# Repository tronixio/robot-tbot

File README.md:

# ROBOT - TBOT 2 Wheels.

## TBOT Features.

- 2 Wheels.
- Continuous RC Servos Motors.
- Power 2xCells 18650 Lithium Ion Rechargeable Batteries, with embedded charger.
- [PARALLAX Small Robot Chassis.](https://www.parallax.com/product/700-00022)
- [PARALLAX Feedback 360 High Speed Servo.](https://www.parallax.com/product/900-00360)
- [PARALLAX Small Robot Whell and Tire.](https://www.parallax.com/product/28114)
- [PARALLAX 1" Tail Whell Ball.](https://www.parallax.com/product/700-00009)

## TBOT All Schematics.

- [DRAFT - MCU Board PIC-8BIT.](https://github.com/tronixio/robot-tbot/)
- [Charger 2x18650.](https://github.com/tronixio/robot-tbot/blob/main/Kicad/charger/extras/schematic.pdf)
- [DRAFT - IR Wheel.](https://github.com/tronixio/robot-tbot/)
- [Sensor GP2Y.](https://github.com/tronixio/robot-tbot/blob/main/Kicad/gp2y/extras/schematic.pdf)
- [DRAFT - Sensor HC-SR04.](https://github.com/tronixio/robot-tbot/)
- [DRAFT - IR Line Folllow.](https://github.com/tronixio/robot-tbot/)

## TBOT Code.

- [PIC16F1778 - MCU & GPIO Configuration.](https://github.com/tronixio/robot-tbot/blob/main/Code/configuration/)
- [PIC16F1778 - EUSART TX - Display Strings.](https://github.com/tronixio/robot-tbot/blob/main/Code/eusart-tx/)
- [PIC16F1778 - EUSART TX/RX - Echo RX Character.](https://github.com/tronixio/robot-tbot/blob/main/Code/eusart-txrx/)
- [PIC16F1778 - ADC/TIMER0 - Read, Display & Check Battery Value.](https://github.com/tronixio/robot-tbot/blob/main/Code/adc/)
- [PIC16F1778 - PWM 16-Bit - RC Servo Forward & Backward.](https://github.com/tronixio/robot-tbot/blob/main/Code/pwm/)
- [PIC16F1778 - INT0 - Emergency Switch & LED.](https://github.com/tronixio/robot-tbot/blob/main/Code/int0/)
- [PIC16F1778 - IOC - Sharp GP2Y0D21YK.](https://github.com/tronixio/robot-tbot/blob/main/Code/gp2y0d21yk/)

## TBOT Firmware.

- [DRAFT - PIC16F1778 - PIC-AS - Firmware SHARP GP2Y0D21YK.](https://github.com/tronixio/robot-tbot/blob/main/MplabX/PICAS-P16F1778-GP2Y0D21YK.X/)

<!--
* [PIC16F1778 - XC8 - Firmware DEBUG.](https://github.com/tronixio/robot-tbot/tree/main/MplabX/XC8-P16F1778-DEBUG.X/)
* [TBOT Firmware - Sharp GP2Y0D21YK.](https://github.com/tronixio/robot-tbot/tree/main/MplabX/PICAS-P16F1778-GP2Y0D21YK.X)
* [TBOT Firmware - Sharp GP2Y0A21YK.](https://github.com/tronixio/robot-tbot/tree/main/MplabX/PICAS-P16F1778-GP2Y0A21YK.X)
* [TBOT Firmware - HC SR04.](https://github.com/tronixio/robot-tbot/tree/main/MplabX/PICAS-P16F1778-HCSR04.X)
-->

## DRAFT - TBOT MCU PIC 8Bit Top.

## DRAFT - TBOT MCU PIC 8Bit Bottom.

## TBOT Charger Top.

## TBOT Charger Bottom.

## DRAFT - TBOT IR Wheel Top.

## DRAFT - TBOT IR Wheel Bottom.

## TBOT GP2Y Top.

## TBOT GP2Y Bottom.

## DRAFT - TBOT HC-SR04 Top.

## DRAFT - TBOT HC-SR04 Bottom.

## DRAFT - TBOT IR Line Follow Top.

## DRAFT - TBOT IR Line Follow Bottom.

!!! note

    - DRAFT : Prototype OK, last check schematic, PCB & code can be modify.
    - TODO : Work in progress, prototype was not good, hardware, PCB and code can be rework.

!!! example "DISCLAIMER"

    THIS CODE IS PROVIDED WITHOUT ANY WARRANTY OR GUARANTEES.
    USERS MAY USE THIS CODE FOR DEVELOPMENT AND EXAMPLE PURPOSES ONLY.
    AUTHORS ARE NOT RESPONSIBLE FOR ANY ERRORS, OMISSIONS, OR DAMAGES THAT COULD
    RESULT FROM USING THIS FIRMWARE IN WHOLE OR IN PART.

---

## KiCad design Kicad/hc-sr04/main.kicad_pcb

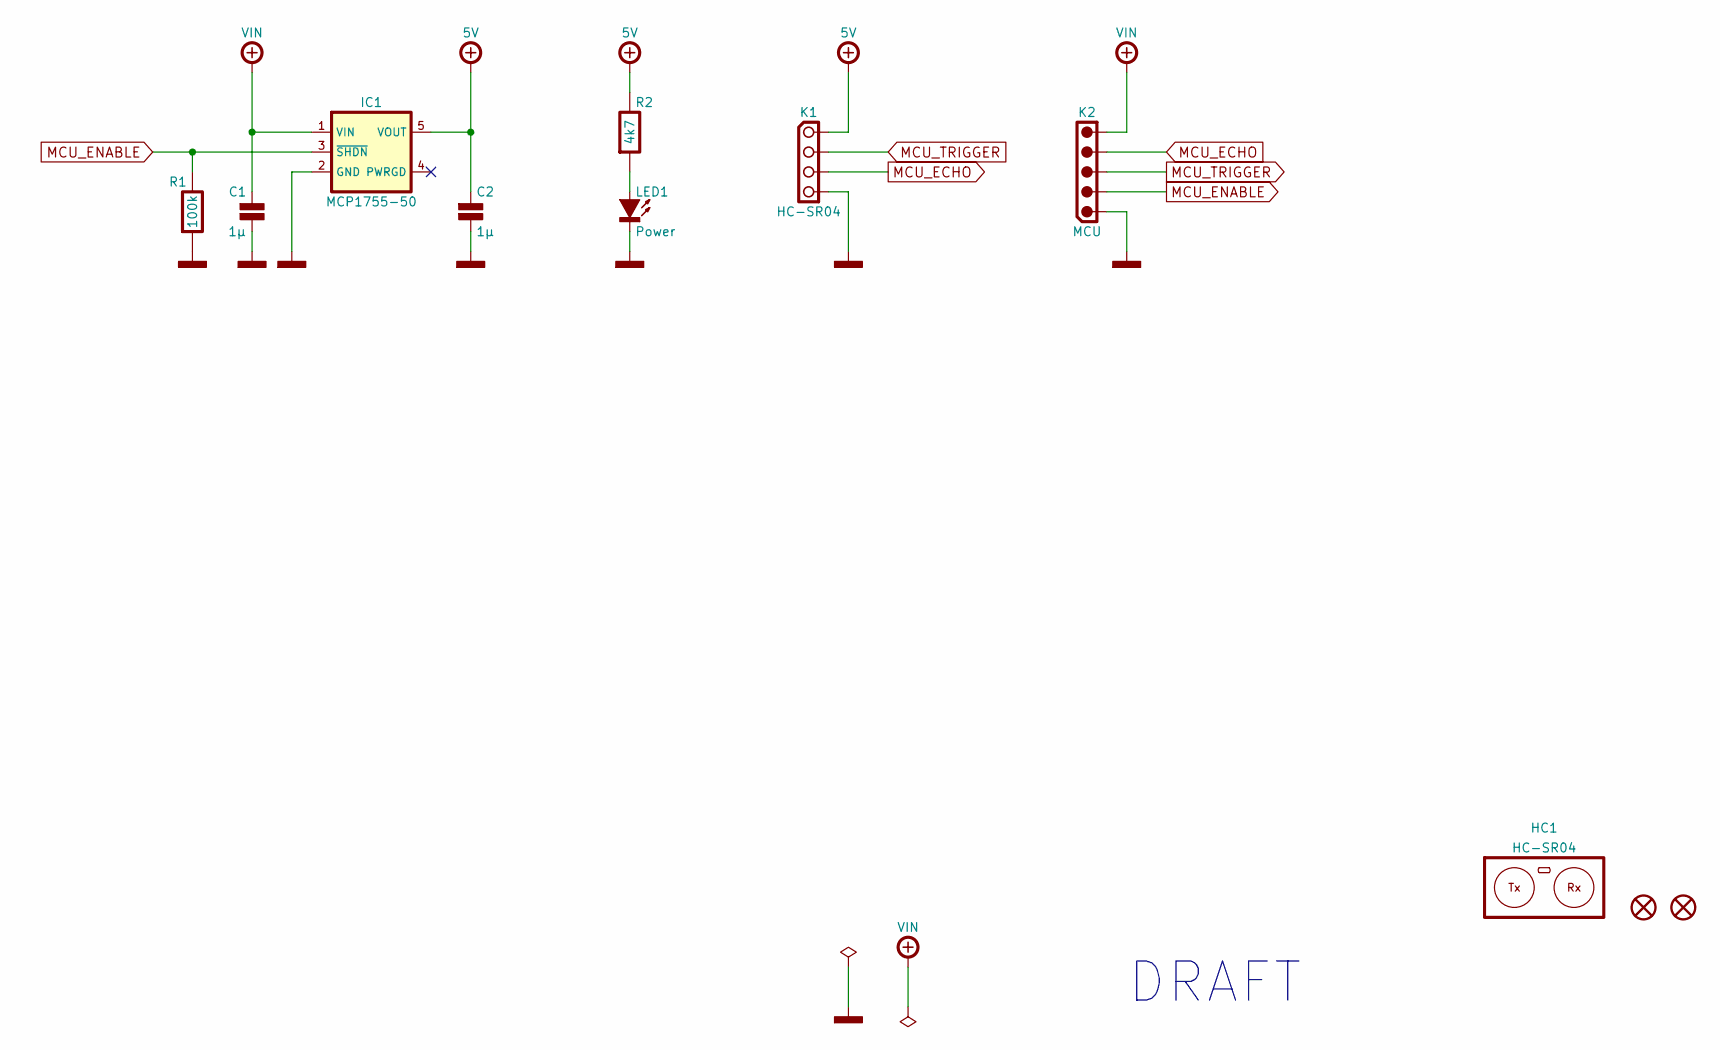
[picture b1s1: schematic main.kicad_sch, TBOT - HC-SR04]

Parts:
C1, C2: 1µ; CAPACITOR-SMD-1206; Voltage 16V; Tolerance 10%; Mouser 80-C1206C105K4R
H1, H2: MOUNTING-HOLE-3MM-MASK
HC1: HC-SR04
IC1: MCP1755-50; SOT-23-5; Mouser 579-MCP1755T-5002EOT
K1: HC-SR04; SAMTEC-SSW-104-02-T-S-RA; Mouser 200-SSW10402TSRA
K2: MCU; MOLEX-532540570; Mouser 538-53254-0570
LED1: Power; LED-SMD-1206; Mouser 604-APTR3216-VFX
R1: 100k; RESISTOR-SMD-1206; Tolerance 5%; Mouser 660-RK73B2BTTDD104J
R2: 4k7; RESISTOR-SMD-1206; Tolerance 5%; Mouser 660-RK73B2BTTDD472J

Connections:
+5V: C2.1, IC1.5 (VOUT), K1.1, R2.1
+VIN: C1.1, IC1.1 (VIN), K2.5
GND: C1.2, C2.2, IC1.2 (GND), K1.4, K2.1, LED1.1 (C), R1.2
MCU_ECHO: K1.3, K2.4
MCU_ENABLE: IC1.3 (~SHDN), K2.2, R1.1
MCU_TRIGGER: K1.2, K2.3
unnamed: LED1.2 (A), R2.2

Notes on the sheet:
DRAFT

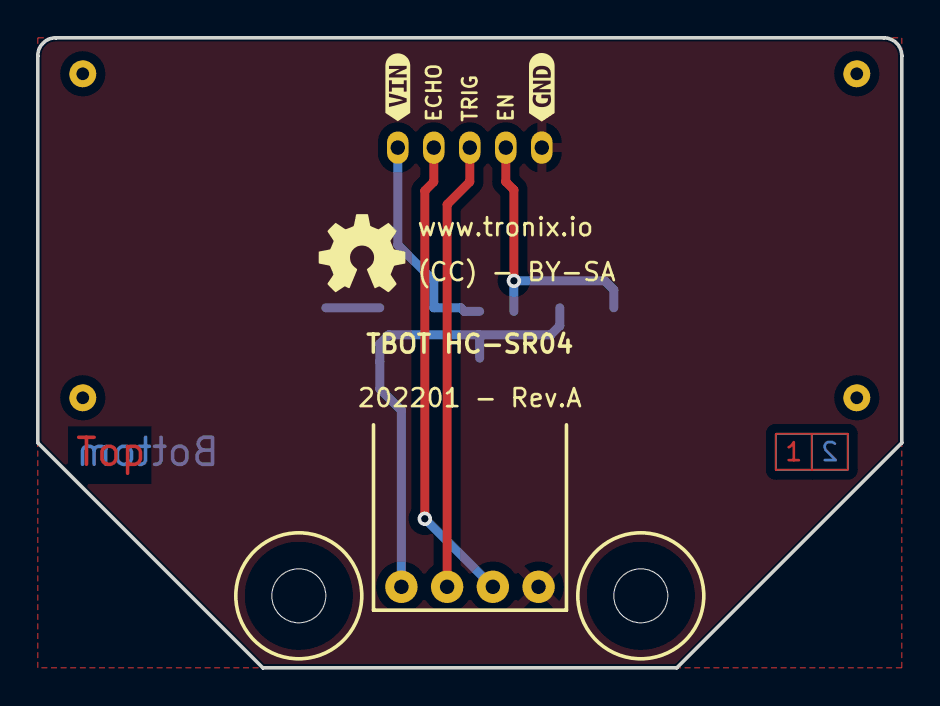
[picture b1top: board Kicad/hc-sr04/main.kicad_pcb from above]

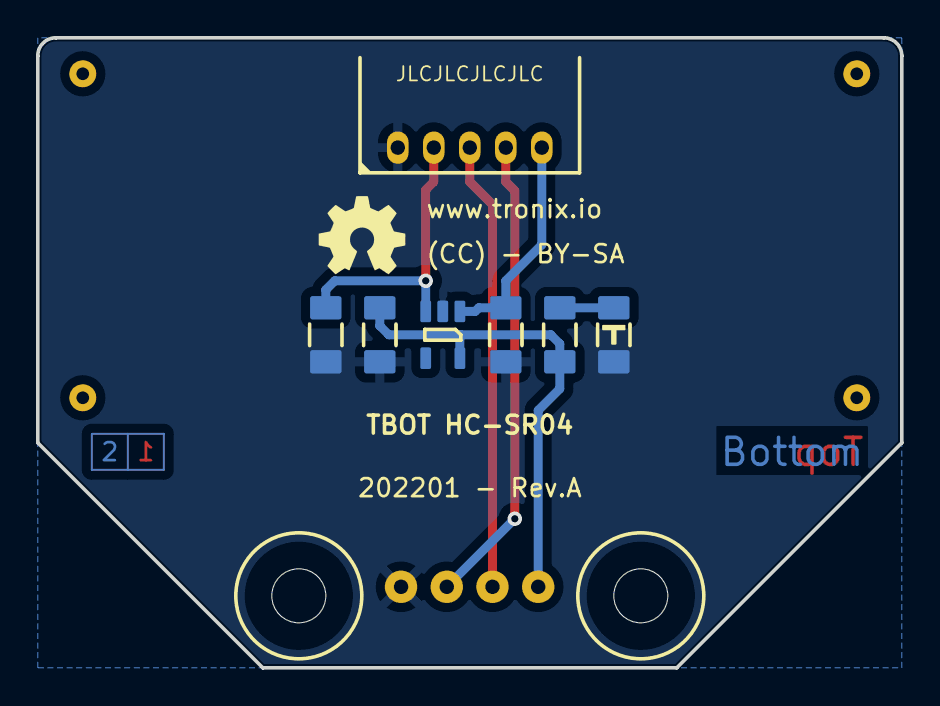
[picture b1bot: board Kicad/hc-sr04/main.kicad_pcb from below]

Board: 2 copper layers, 48.0 x 35.0 mm, 15 parts (10 on the bottom side), 7 nets.

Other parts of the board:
GB: LOGO; OSHW-5MM
GT: LOGO; OSHW-5MM
kibuzzard-6288C61E: G***; kibuzzard-6288C61E
kibuzzard-6288C626: G***; kibuzzard-6288C626

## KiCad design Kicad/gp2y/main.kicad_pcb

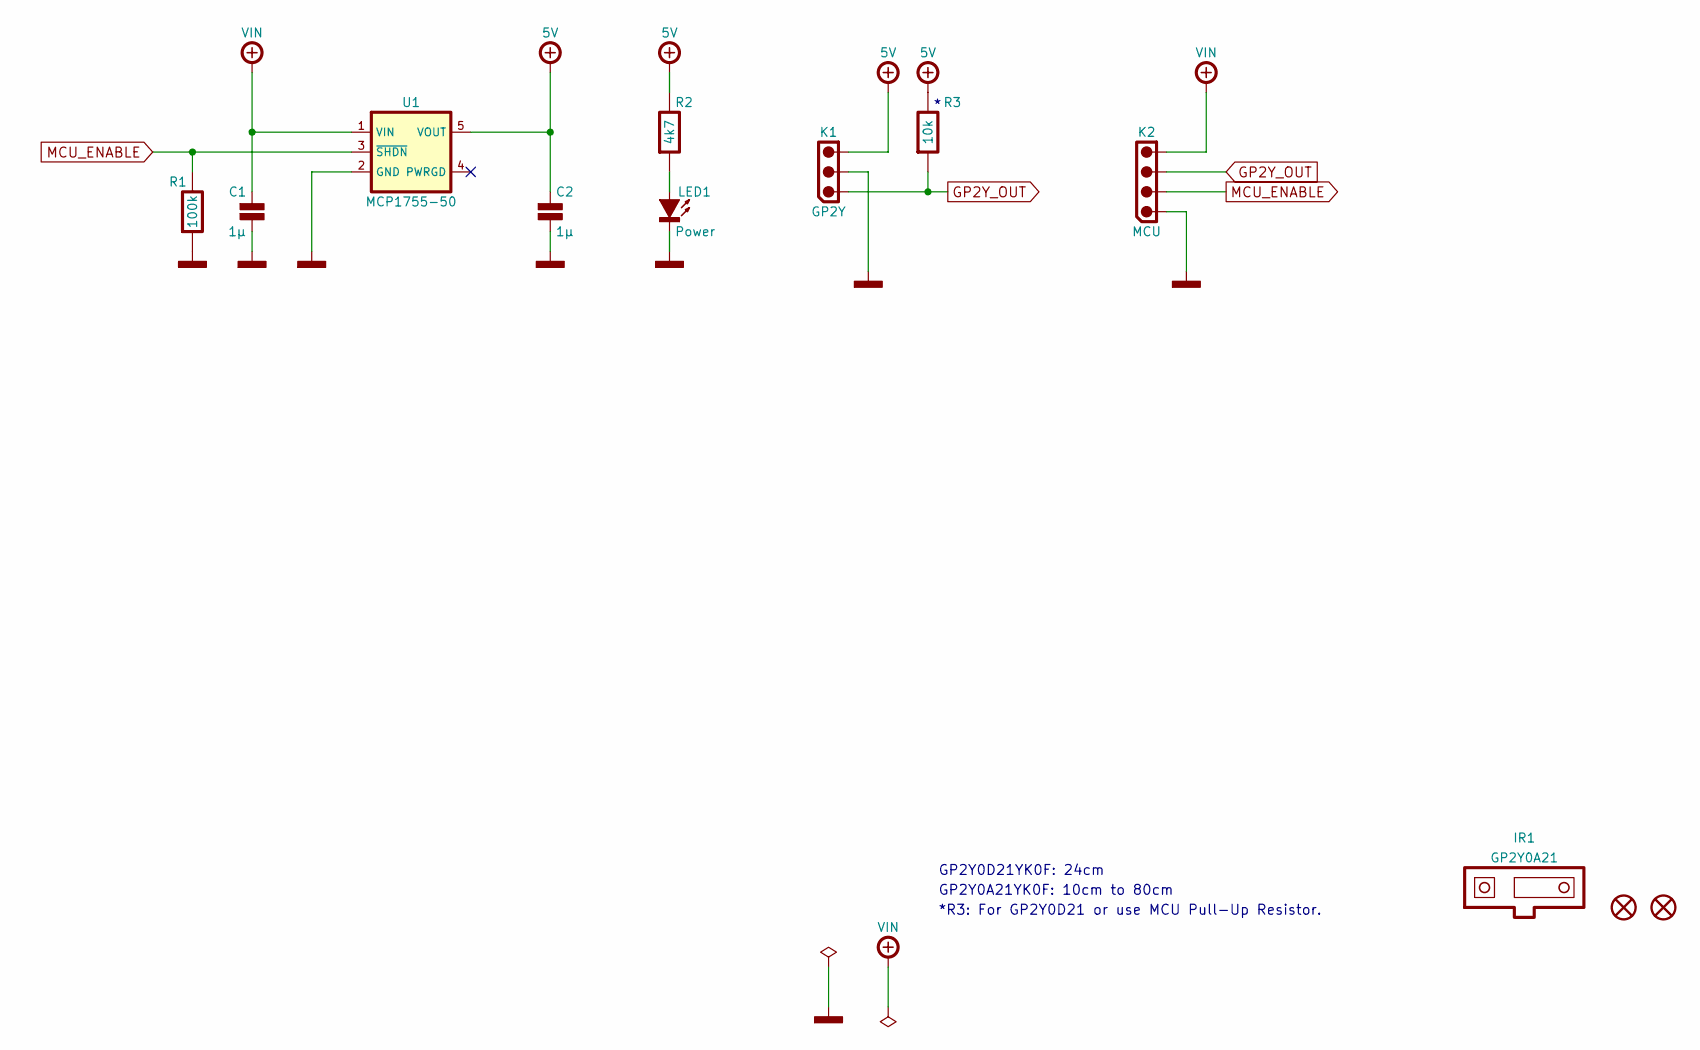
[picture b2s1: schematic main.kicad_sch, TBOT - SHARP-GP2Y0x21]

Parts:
C1, C2: 1µ; CAPACITOR-SMD-1206; Voltage 16V; Tolerance 10%; Mouser 80-C1206C105K4R
H1, H2: MOUNTING-HOLE-3MM-MASK
IR1: GP2Y0A21; SHARP-GP2Y0A; Mouser 852-GP2Y0A21YK0F
K1: GP2Y; MOLEX-532540370; Mouser 538-53254-0370
K2: MCU; MOLEX-532540470; Mouser 538-53254-0470
LED1: Power; LED-SMD-1206; Mouser 604-APTR3216-VFX
R1: 100k; RESISTOR-SMD-1206; Tolerance 5%; Mouser 660-RK73B2BTTDD104J
R2: 4k7; RESISTOR-SMD-1206; Tolerance 5%; Mouser 660-RK73B2BTTDD472J
R3: 10k; RESISTOR-SMD-1206; Tolerance 5%; Mouser 660-RK73B2BTTDD103J
U1: MCP1755-50; SOT-23-5; Mouser 579-MCP1755T-5002EOT

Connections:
+5V: C2.1, K1.3, R2.1, R3.1, U1.5 (VOUT)
+VIN: C1.1, K2.4, U1.1 (VIN)
GND: C1.2, C2.2, K1.2, K2.1, LED1.1 (C), R1.2, U1.2 (GND)
GP2Y_OUT: K1.1, K2.3, R3.2
MCU_ENABLE: K2.2, R1.1, U1.3 (~SHDN)
unnamed: LED1.2 (A), R2.2

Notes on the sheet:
GP2Y0D21YK0F: 24cm
GP2Y0A21YK0F: 10cm to 80cm
*R3: For GP2Y0D21 or use MCU Pull-Up Resistor.

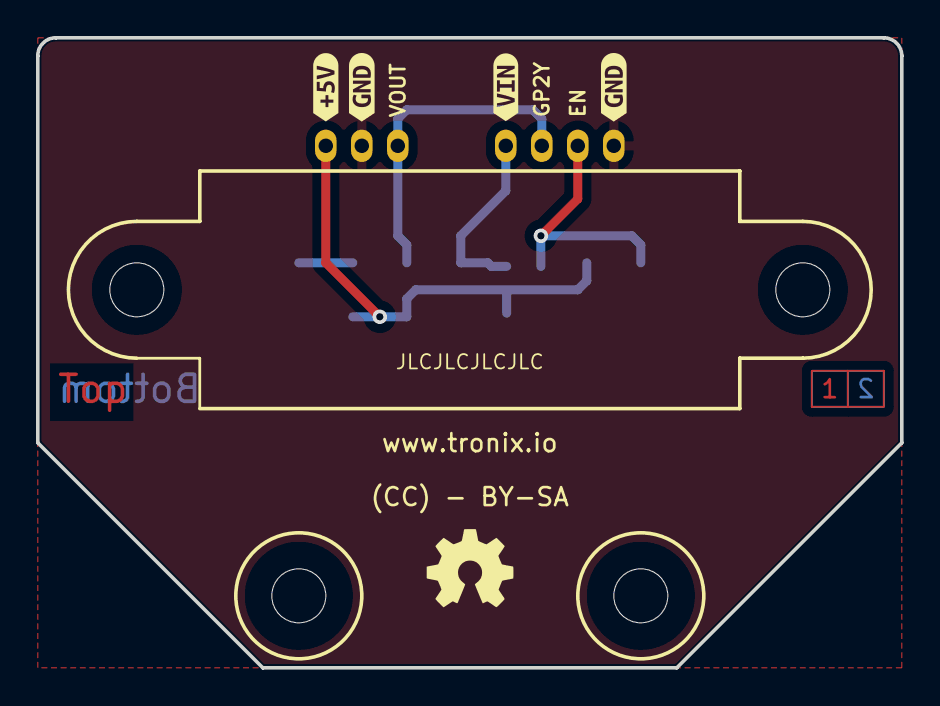
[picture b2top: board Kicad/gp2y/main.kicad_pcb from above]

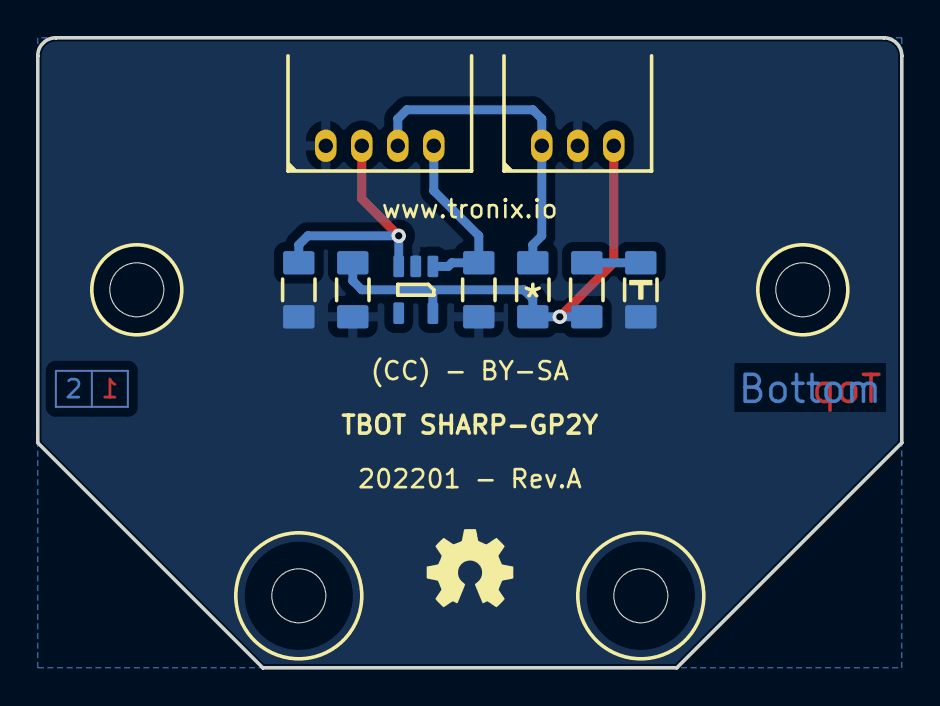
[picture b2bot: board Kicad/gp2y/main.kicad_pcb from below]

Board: 2 copper layers, 48.0 x 35.0 mm, 18 parts (12 on the bottom side), 6 nets.

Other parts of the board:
GB: LOGO; OSHW-5MM
GT: LOGO; OSHW-5MM
kibuzzard-6288C56E: G***; kibuzzard-6288C56E
kibuzzard-6288C554: G***; kibuzzard-6288C554
kibuzzard-6288C562: G***; kibuzzard-6288C562
kibuzzard-6288C567: G***; kibuzzard-6288C567

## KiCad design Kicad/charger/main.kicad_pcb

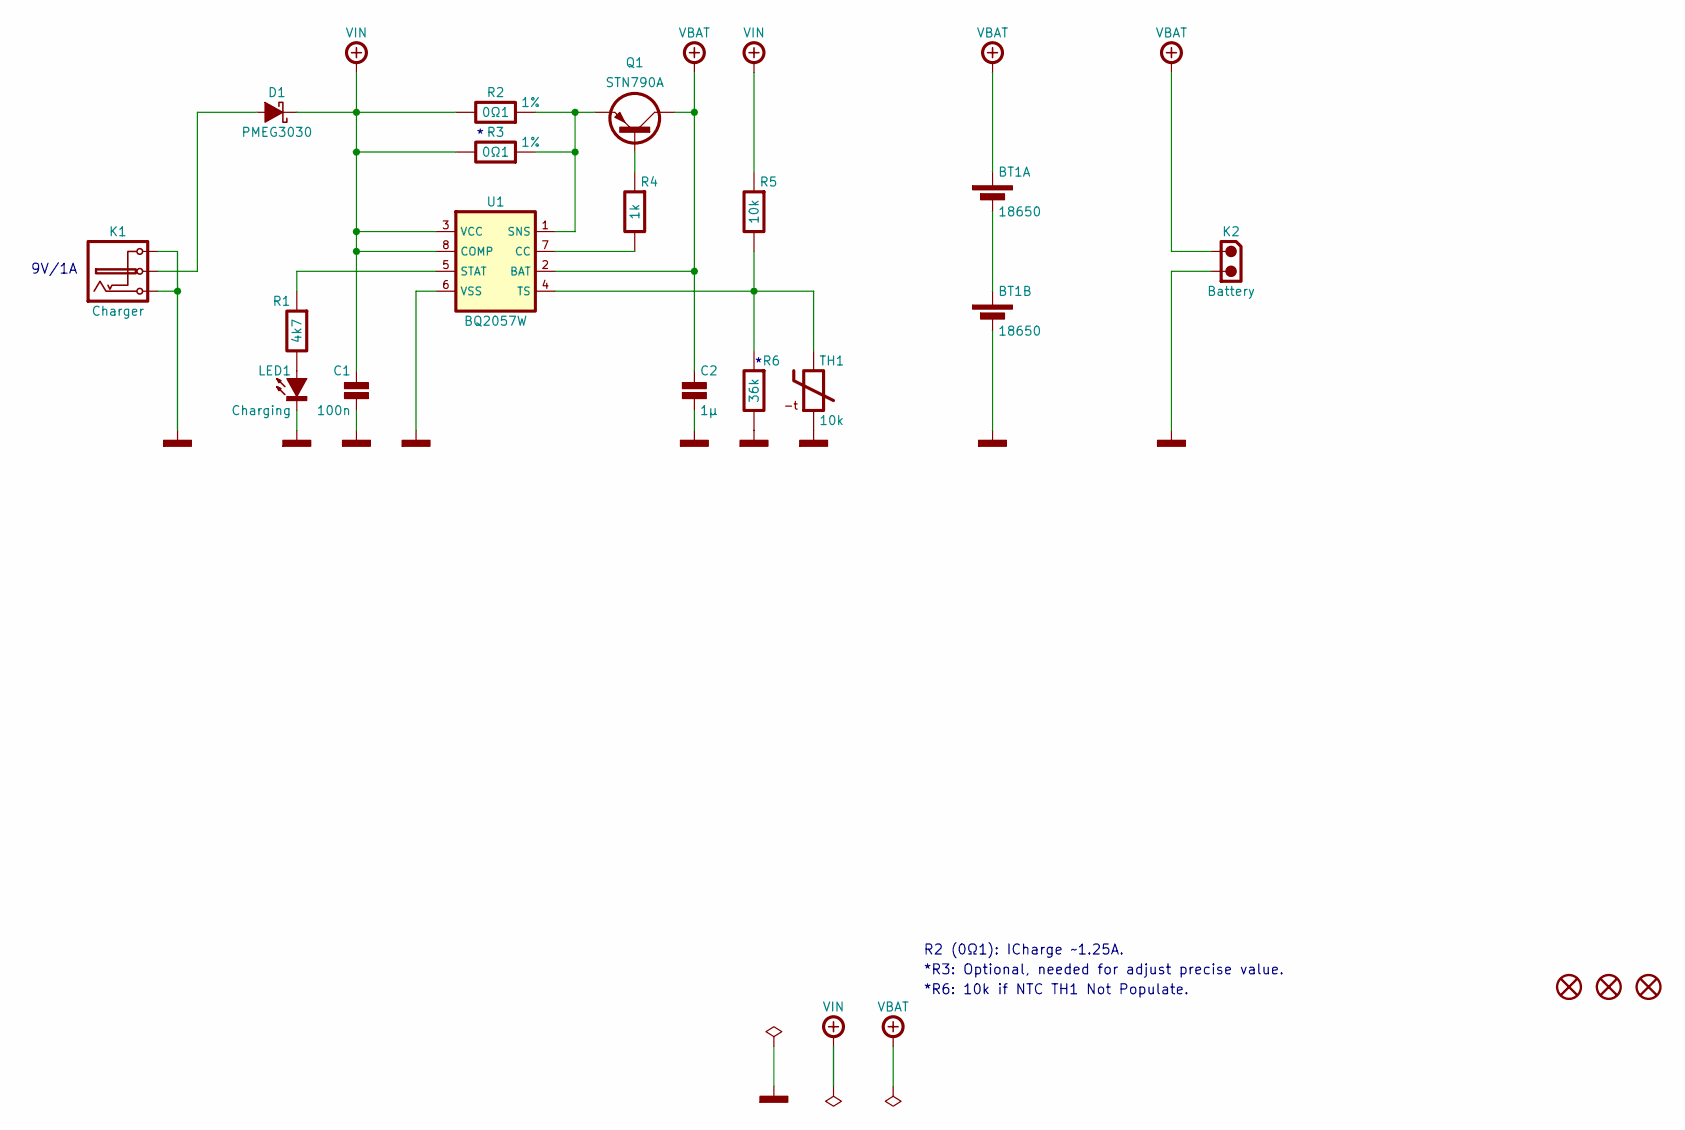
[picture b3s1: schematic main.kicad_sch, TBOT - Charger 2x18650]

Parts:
BT1: 18650; KEYSTONE-1049; Mouser 534-1049
C1: 100n; CAPACITOR-SMD-1206; Voltage 50V; Tolerance 5%; Mouser 80-C1206C104J5R
C2: 1µ; CAPACITOR-SMD-1206; Voltage 16V; Tolerance 10%; Mouser 80-C1206C105K4R
D1: PMEG3030; SOD-128; Mouser 771-PMEG3030EP115
H1, H2, H3: MOUNTING-HOLE-3MM-MASK
K1: Charger; CUI-PJ-102AH; Mouser 490-PJ-102AH
K2: Battery; MOLEX-22057025; Mouser 538-22-05-7025
LED1: Charging; LED-SMD-1206; Mouser 604-APTR3216-VFX
Q1: STN790A; SOT-223-3; Mouser 511-STN790A
R1: 4k7; RESISTOR-SMD-1206; Tolerance 5%; Mouser 660-RK73B2BTTDD472J
R2, R3: 0Ω1; RESISTOR-SMD-1210; Tolerance 1%; Mouser 660-SR732ETTER100F
R4: 1k; RESISTOR-SMD-1206; Tolerance 5%; Mouser 660-RK73B2BTTDD102J
R5: 10k; RESISTOR-SMD-1206; Tolerance 5%; Mouser 660-RK73B2BTTDD103J
R6: 36k; RESISTOR-SMD-1206; Tolerance 5%; Mouser 660-RK73B2BTTDD363J
TH1: 10k; THERMISTOR-SMD; Mouser 594-NTCLE213E3103FL
U1: BQ2057W; SOIC-08; Mouser 595-BQ2057WSN

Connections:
+VBAT: BT1.2 (+), C2.1, K2.1, Q1.2 (C), U1.2 (BAT)
+VIN: C1.1, D1.1 (C), R2.1, R3.1, R5.2, U1.3 (VCC), U1.8 (COMP)
GND: BT1.3 (-), C1.2, C2.2, K1.2, K1.3, K2.2, LED1.1 (C), R6.1, TH1.2, U1.6 (VSS)
unnamed: BT1.1 (-), BT1.4 (+)
unnamed: D1.2 (A), K1.1
unnamed: LED1.2 (A), R1.1
unnamed: Q1.1 (B), R4.2
unnamed: Q1.3 (E), R2.2, R3.2, U1.1 (SNS)
unnamed: R4.1, U1.7 (CC)
unnamed: R1.2, U1.5 (STAT)
unnamed: R5.1, R6.2, TH1.1, U1.4 (TS)

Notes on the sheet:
R2 (0Ω1): ICharge ~1.25A.
*R3: Optional, needed for adjust precise value.
*R6: 10k if NTC TH1 Not Populate.
9V/1A

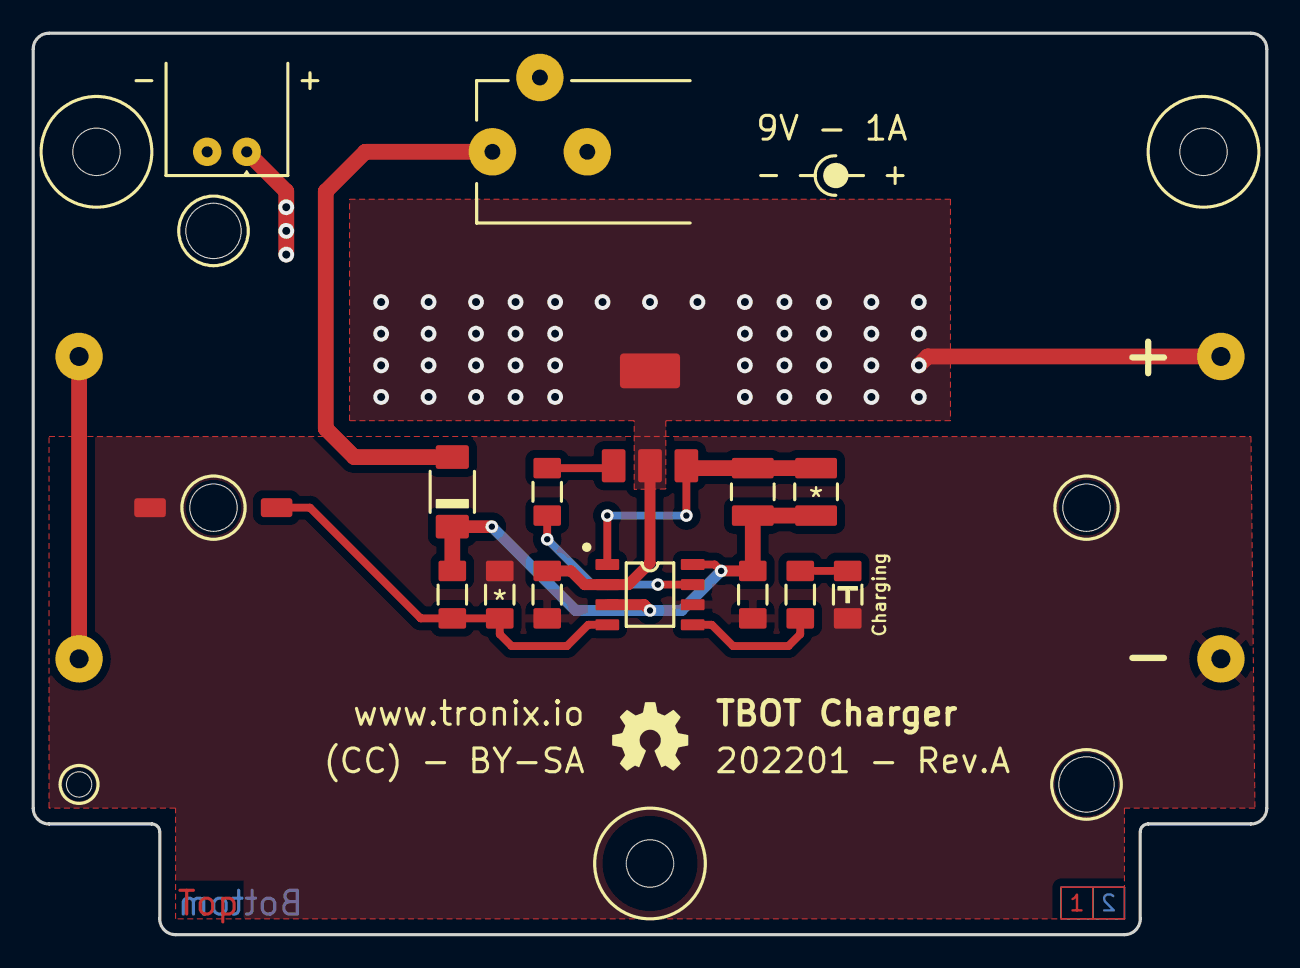
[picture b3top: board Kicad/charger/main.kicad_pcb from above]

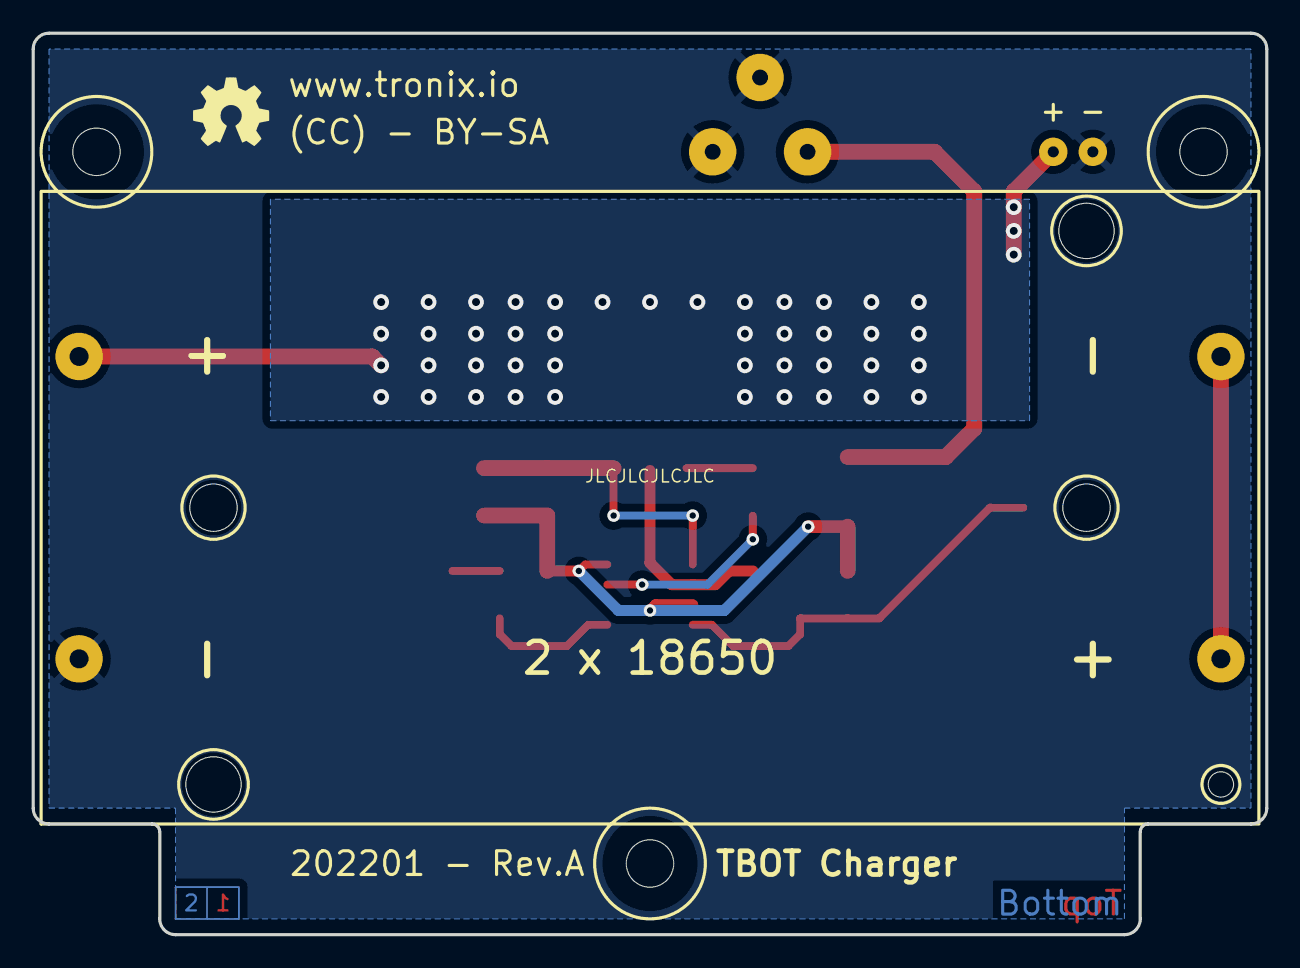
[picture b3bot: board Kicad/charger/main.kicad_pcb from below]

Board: 2 copper layers, 78.0 x 57.0 mm, 21 parts (5 on the bottom side), 11 nets.

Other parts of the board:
GB: LOGO; OSHW-5MM
GT: LOGO; OSHW-5MM

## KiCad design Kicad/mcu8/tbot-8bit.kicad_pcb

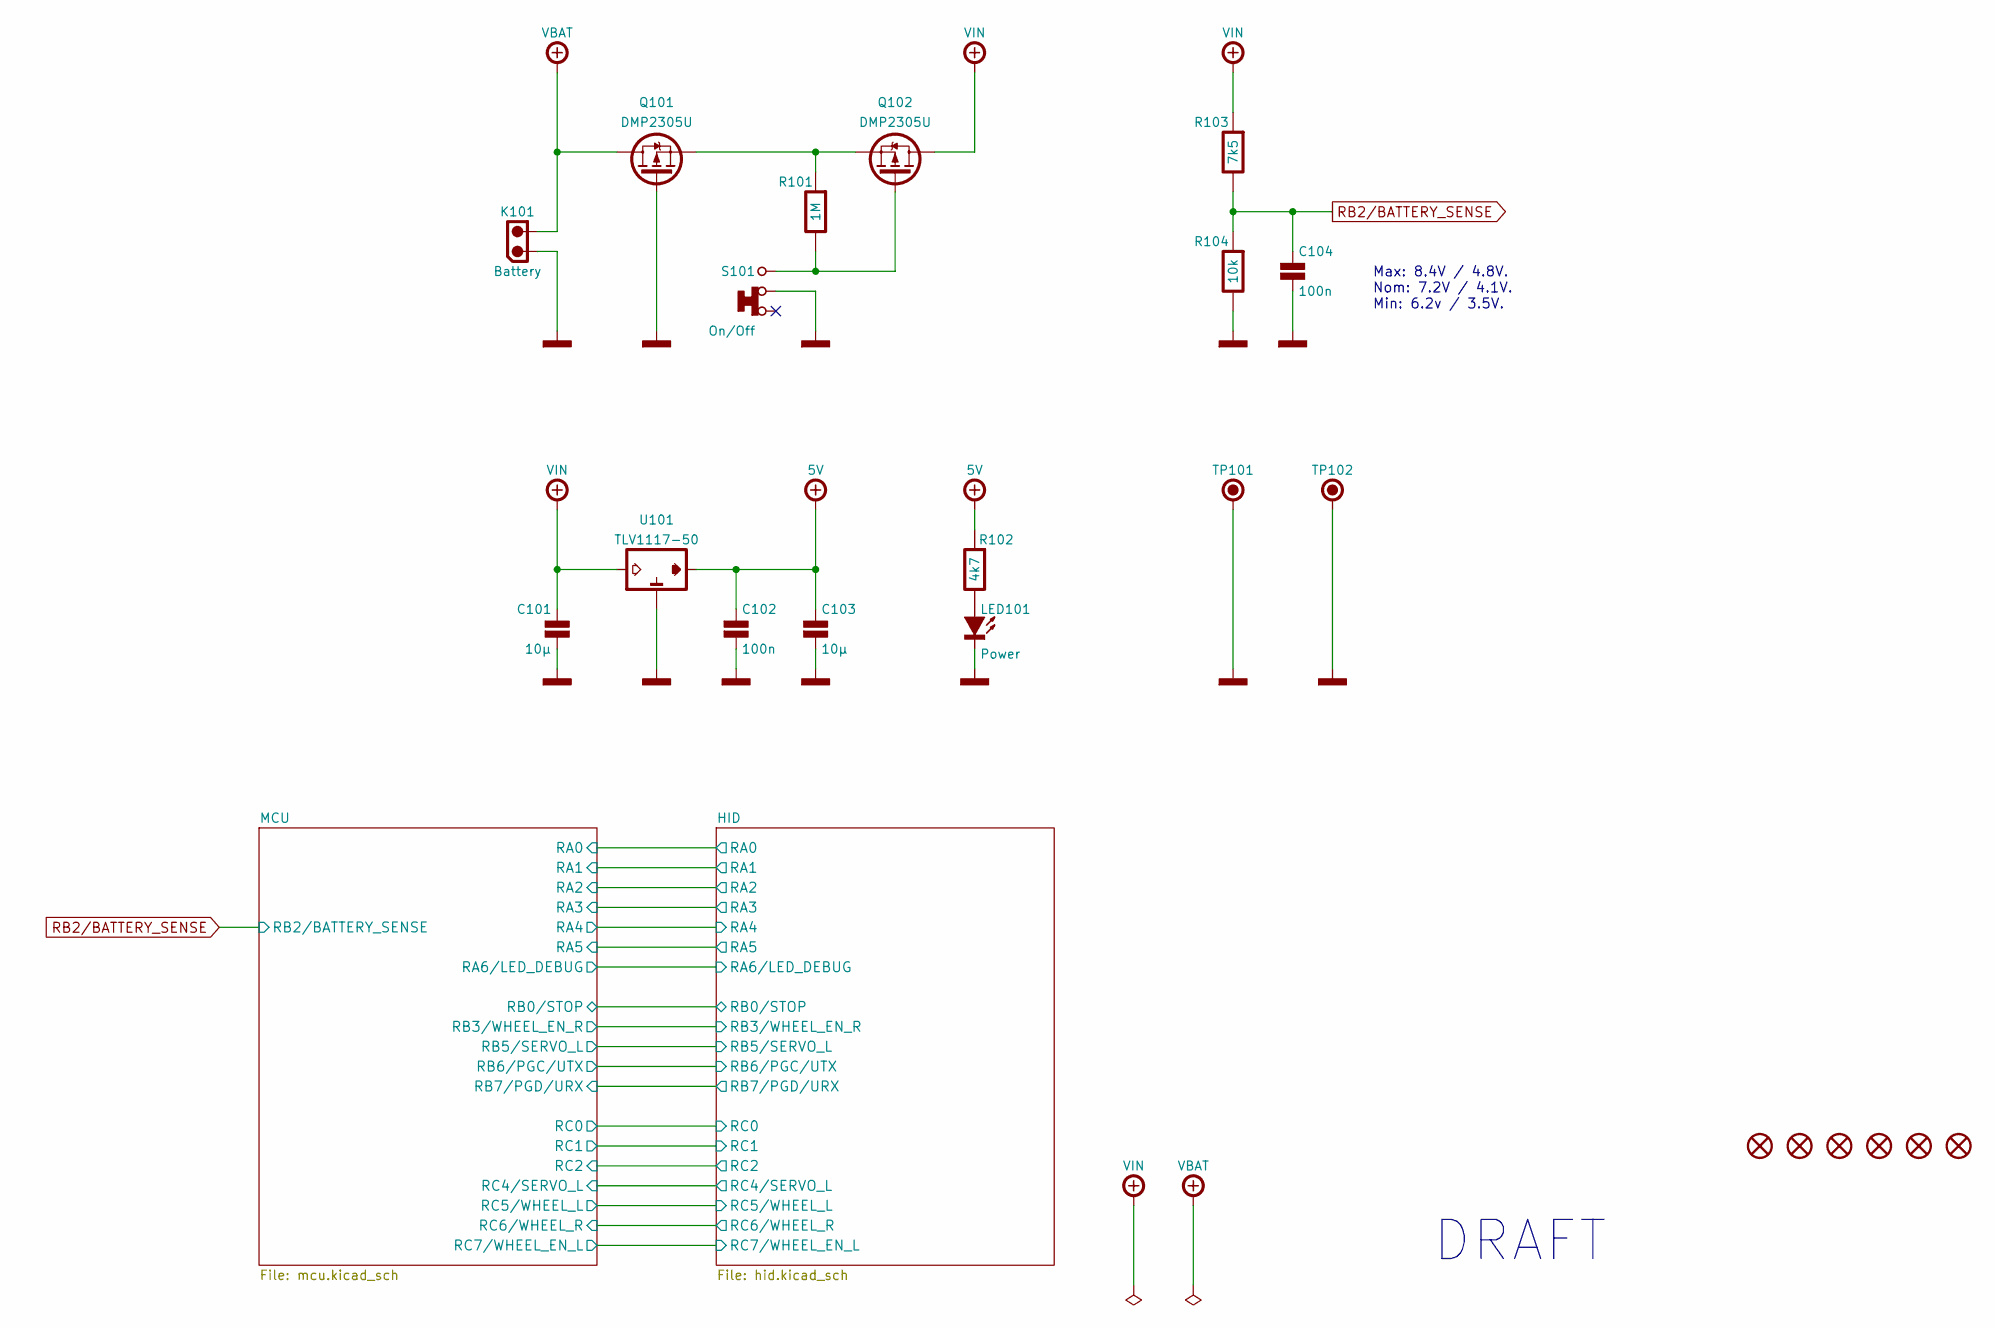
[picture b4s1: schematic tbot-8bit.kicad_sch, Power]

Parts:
C101, C103: 10µ; CAPACITOR-SMD-1206; Voltage 25V; Tolerance 5%; Mouser 80-C1206C106J3R
C102, C104: 100n; CAPACITOR-SMD-1206; Voltage 50V; Tolerance 5%; Mouser 80-C1206C104J5R
H101, H102, H103, H104, H105, H106: MOUNTING-HOLE-3MM-MASK
K101: Battery; MOLEX-22057025; Mouser 538-22-05-7025
LED101: Power; LED-SMD-1206; Mouser 604-APTR3216-VFX
Q101, Q102: DMP2305U; SOT-23-3; Mouser 621-DMP2305U-7
R101: 1M; RESISTOR-SMD-1206; Tolerance 5%; Mouser 660-RK73B2BTTDD105J
R102: 4k7; RESISTOR-SMD-1206; Tolerance 5%; Mouser 660-RK73B2BTTDD472J
R103: 7k5; RESISTOR-SMD-1206; Tolerance 5%; Mouser 660-RK73B2BTTD752J
R104: 10k; RESISTOR-SMD-1206; Tolerance 5%; Mouser 660-RK73B2BTTDD103J
S101: On/Off; E-SWITCH-200USPXT1A1M2RE; Mouser 612-200USP1T1A1M2RE
TP101: GND; KEYSTONE-5006; Mouser 534-5006
TP102: GND; KEYSTONE-2000-3; Mouser 534-2000-3
U101: TLV1117-50; SOT-223-3; Mouser 595-TLV1117-50CDC

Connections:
+5V: C102.1, C103.1, R102.2, U101.2 (VO); also elsewhere on the board
+VBAT: K101.2, Q101.3 (D)
+VIN: C101.1, Q102.3 (D), R103.2, U101.3 (VI); also elsewhere on the board
GND: C101.2, C102.2, C103.2, C104.2, K101.1, LED101.1 (C), Q101.1 (G), R104.1, S101.2, TP101.1, TP102.1, U101.1 (GND); also elsewhere on the board
unnamed: LED101.2 (A), R102.1
unnamed: Q101.2 (S), Q102.2 (S), R101.2
unnamed: Q102.1 (G), R101.1, S101.3
RB2/BATTERY_SENSE: C104.1, R103.1, R104.2

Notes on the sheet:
Max: 8.4V / 4.8V. Nom: 7.2V / 4.1V. Min: 6.2v / 3.5V.
DRAFT

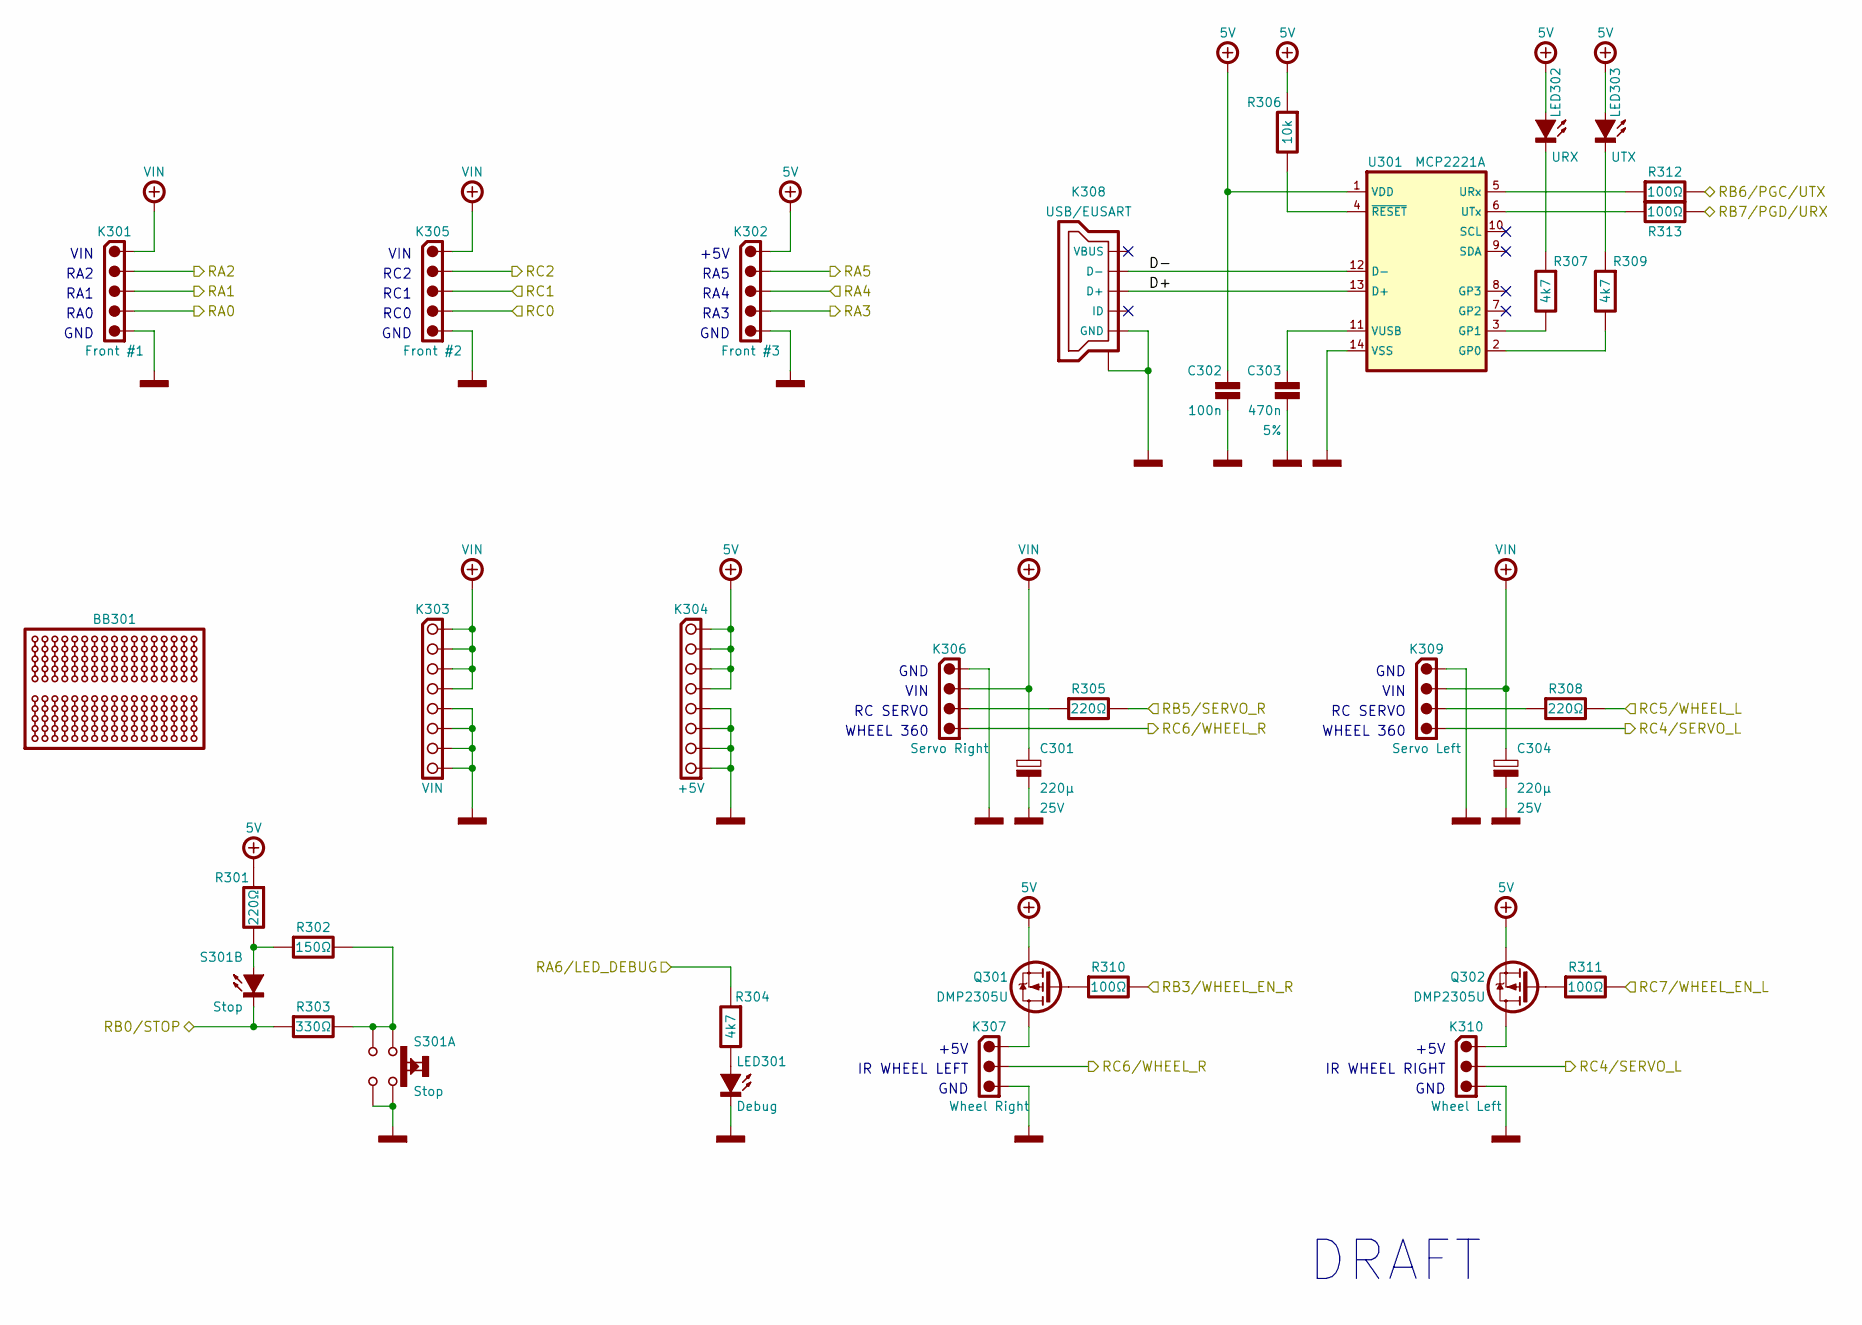
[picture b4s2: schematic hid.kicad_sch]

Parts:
BB301: BREADBOARD-170; Mouser 854-BB170
C301, C304: 220µ; CAPACITOR-ELECTROLYTIC-RADIAL-080-115-035; Voltage 25V; Tolerance 20%; Mouser 647-UVZ1E221MPD
C302: 100n; CAPACITOR-SMD-1206; Voltage 50V; Tolerance 5%; Mouser 80-C1206C104J5R
C303: 470n; CAPACITOR-SMD-1206; Voltage 50V; Tolerance 5%; Mouser 791-1206B474J500CT
K301: Front #1; MOLEX-532530570; Mouser 538-53253-0570
K302: Front #3; MOLEX-532530570; Mouser 538-53253-0570
K303: VIN; HARWIN-M20-782084x; Mouser 855-M20-782084
K304: +5V; HARWIN-M20-782084x; Mouser 855-M20-782084
K305: Front #2; MOLEX-532530570; Mouser 538-53253-0570
K306: Servo Right; HARWIN-M20-999044x; Mouser 855-M20-999044
K307: Wheel Right; MOLEX-532530370; Mouser 538-53253-0370
K308: USB/EUSART; USB-TYPE-B-MICRO-TH; Mouser 649-10118193-0001LF
K309: Servo Left; HARWIN-M20-999044x; Mouser 855-M20-999044
K310: Wheel Left; MOLEX-532530370; Mouser 538-53253-0370
LED301: Debug; LED-SMD-1206; Mouser 604-APTR3216-VFX
LED302: URX; LED-SMD-1206; Mouser 604-APTR3216-VFX
LED303: UTX; LED-SMD-1206; Mouser 604-APTR3216-VFX
Q301, Q302: DMP2305U; SOT-23-3; Mouser 621-DMP2305U-7
R301, R305, R308: 220Ω; RESISTOR-SMD-1206; Tolerance 5%; Mouser 660-RK73B2BTTDD221J
R302: 150Ω; RESISTOR-SMD-1206; Tolerance 5%; Mouser 660-RK73B2BTTDD151J
R303: 330Ω; RESISTOR-SMD-1206; Tolerance 5%; Mouser 660-RK73B2BTTDD331J
R304, R307, R309: 4k7; RESISTOR-SMD-1206; Tolerance 5%; Mouser 660-RK73B2BTTDD472J
R306: 10k; RESISTOR-SMD-1206; Tolerance 5%; Mouser 660-RK73B2BTTDD103J
R310, R311, R312, R313: 100Ω; RESISTOR-SMD-1206; Tolerance 5%; Mouser 660-RK73B2BTTDD101J
S301: Stop; OMRON-B3W9000-X1; Mouser 653-B3W-9000-R1R
U301: MCP2221A; SOIC-14; Mouser 579-MCP2221A-I/SL

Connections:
+5V: C302.1, K302.1, K304.1, K304.2, K304.3, K304.4, LED302.2 (A), LED303.2 (A), Q301.2 (S), Q302.2 (S), R301.2, R306.2, U301.1 (VDD); also elsewhere on the board
+VIN: C301.1, C304.1, K301.1, K303.1, K303.2, K303.3, K303.4, K305.1, K306.2, K309.2; also elsewhere on the board
/HID/D+: K308.3 (D+), U301.13 (D+)
/HID/D-: K308.2 (D-), U301.12 (D-)
/HID/RA0: K301.4; also elsewhere on the board
/HID/RA1: K301.3; also elsewhere on the board
/HID/RA2: K301.2; also elsewhere on the board
/HID/RA3: K302.4; also elsewhere on the board
/HID/RA4: K302.3; also elsewhere on the board
/HID/RA5: K302.2; also elsewhere on the board
/HID/RA6/LED_DEBUG: R304.2; also elsewhere on the board
/HID/RB0/STOP: R303.2, S301.5 (C); also elsewhere on the board
/HID/RB3/WHEEL_EN_R: R310.1; also elsewhere on the board
/HID/RB5/SERVO_R: R305.1
/HID/RC0: K305.4; also elsewhere on the board
/HID/RC1: K305.3; also elsewhere on the board
/HID/RC2: K305.2; also elsewhere on the board
/HID/RC4/SERVO_L: K309.4, K310.2; also elsewhere on the board
/HID/RC5/WHEEL_L: R308.1; also elsewhere on the board
/HID/RC6/WHEEL_R: K306.4, K307.2; also elsewhere on the board
/HID/RC7/WHEEL_EN_L: R311.1; also elsewhere on the board
GND: C301.2, C302.2, C303.2, C304.2, K301.5, K302.5, K303.5, K303.6, K303.7, K303.8, K304.5, K304.6, K304.7, K304.8, K305.5, K306.1, K307.3, K308.5 (GND), K308.SH (SHIELD), K309.1, K310.3, LED301.1 (C), S301.3, S301.4, U301.14 (VSS); also elsewhere on the board
unnamed: K306.3, R305.2
unnamed: K309.3, R308.2
unnamed: LED301.2 (A), R304.1
unnamed: LED302.1 (C), R307.2
unnamed: LED303.1 (C), R309.2
unnamed: K307.1, Q301.3 (D)
unnamed: Q301.1 (G), R310.2
unnamed: K310.1, Q302.3 (D)
unnamed: Q302.1 (G), R311.2
unnamed: R302.1, R303.1, S301.1, S301.2
unnamed: R301.1, R302.2, S301.6 (A)
unnamed: R309.1, U301.2 (GP0)
unnamed: R307.1, U301.3 (GP1)
unnamed: R312.2, U301.5 (URx)
unnamed: R313.2, U301.6 (UTx)
unnamed: C303.1, U301.11 (VUSB)
unnamed: R306.1, U301.4 (~RESET)
RB6/PGC/UTX: R312.1; also elsewhere on the board
RB7/PGD/URX: R313.1; also elsewhere on the board

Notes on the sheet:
GND
RC0
IR WHEEL RIGHT
VIN
IR WHEEL LEFT
+5V
RA2
RA5
RC1
WHEEL 360
RA3
RC SERVO
RA4
DRAFT
RA0
RC2
RA1
